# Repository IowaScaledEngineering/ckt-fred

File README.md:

# ckt-fred
Circuit for Battery/Track Powered FRED

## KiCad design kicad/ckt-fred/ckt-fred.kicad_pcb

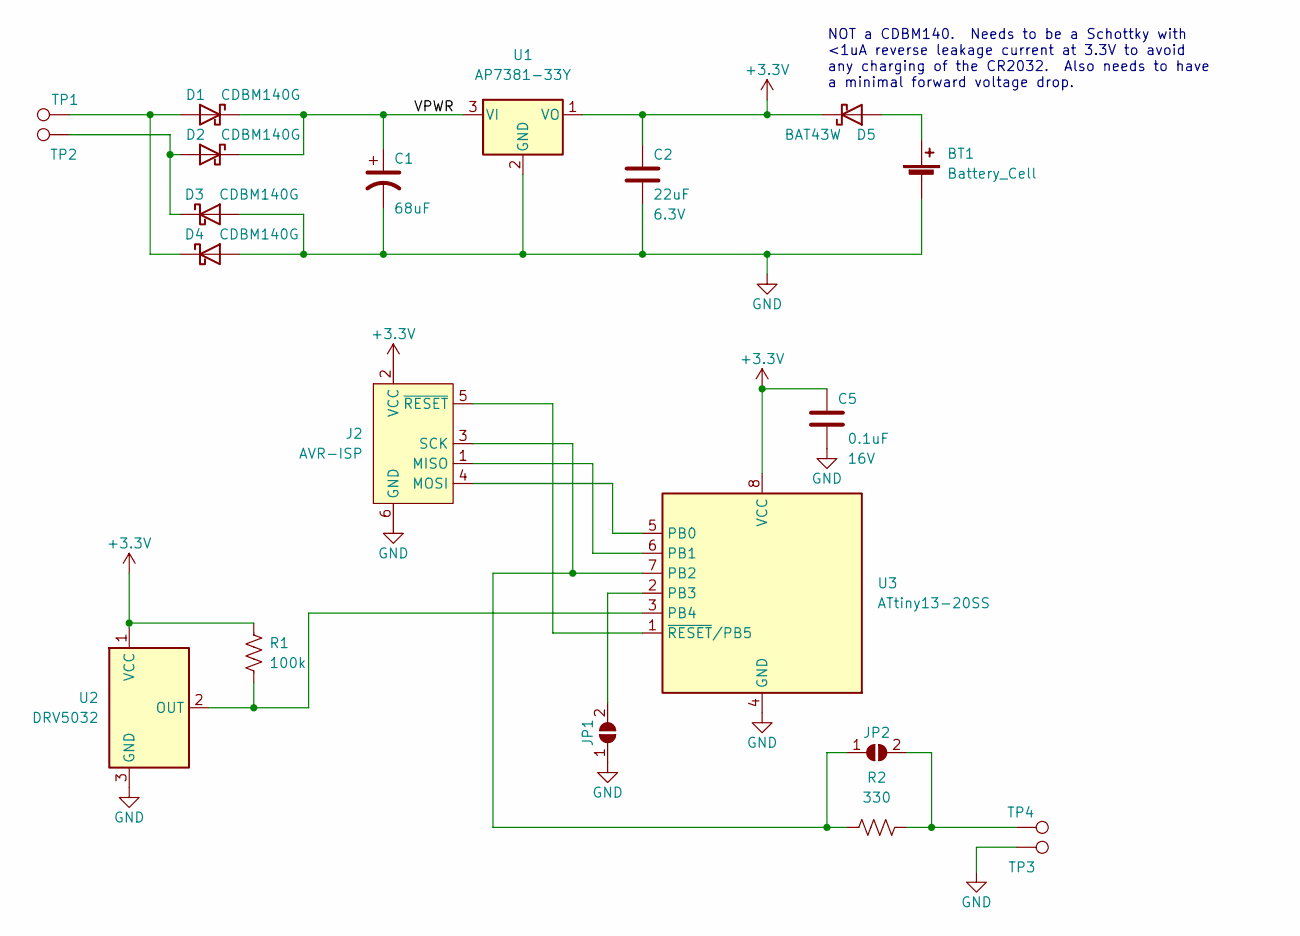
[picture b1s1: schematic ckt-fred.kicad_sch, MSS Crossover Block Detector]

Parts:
BT1: Battery_Cell; BatteryHolder_Keystone_3034_1x20mm
C1: 68uF; CP_Elec_6.3x5.8
C2: 22uF; C_0805_2012Metric; Voltage 6.3V
C5: 0.1uF; C_0805_2012Metric; Voltage 16V
D1, D2, D3, D4: CDBM140G; SOD-123T
D5: BAT43W; SOD-123T
J2: AVR-ISP; Tag-Connect_TC2030-IDC-NL_2x03_P1.27mm_Vertical
JP1, JP2: SolderJumper_2_Open; SolderJumper-2_P1.3mm_Open_RoundedPad1.0x1.5mm
R1: 100k; R_0805_2012Metric
R2: 330; R_0805_2012Metric
TP1, TP2, TP3, TP4: TestPoint; TestPoint_Pad_4.0x4.0mm
U1: AP7381-33Y; SOT-89-3
U2: DRV5032; SOT-23
U3: ATtiny13-20SS; SOIC-8_3.9x4.9mm_P1.27mm

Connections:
+3.3V: C2.1, C5.1, D5.1 (K), J2.2 (VCC), R1.1, U1.1 (VO), U2.1 (VCC), U3.8 (VCC)
/VPWR: C1.1, D1.1 (K), D2.1 (K), U1.3 (VI)
GND: BT1.2 (-), C1.2, C2.2, C5.2, D3.2 (A), D4.2 (A), J2.6 (GND), JP1.1 (A), TP3.1, U1.2 (GND), U2.3 (GND), U3.4 (GND)
unnamed: BT1.1 (+), D5.2 (A)
unnamed: D1.2 (A), D4.1 (K), TP1.1
unnamed: D2.2 (A), D3.1 (K), TP2.1
unnamed: J2.1 (MISO), U3.6 (PB1)
unnamed: J2.3 (SCK), JP2.1 (A), R2.1, U3.7 (PB2)
unnamed: J2.4 (MOSI), U3.5 (PB0)
unnamed: J2.5 (~RESET), U3.1 (~RESET/PB5)
unnamed: JP1.2 (B), U3.2 (PB3)
unnamed: R1.2, U2.2 (OUT), U3.3 (PB4)
unnamed: JP2.2 (B), R2.2, TP4.1

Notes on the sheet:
NOT a CDBM140. Needs to be a Schottky with <1uA reverse leakage current at 3.3V to avoid any charging of the CR2032. Also needs to have a minimal forward voltage drop.

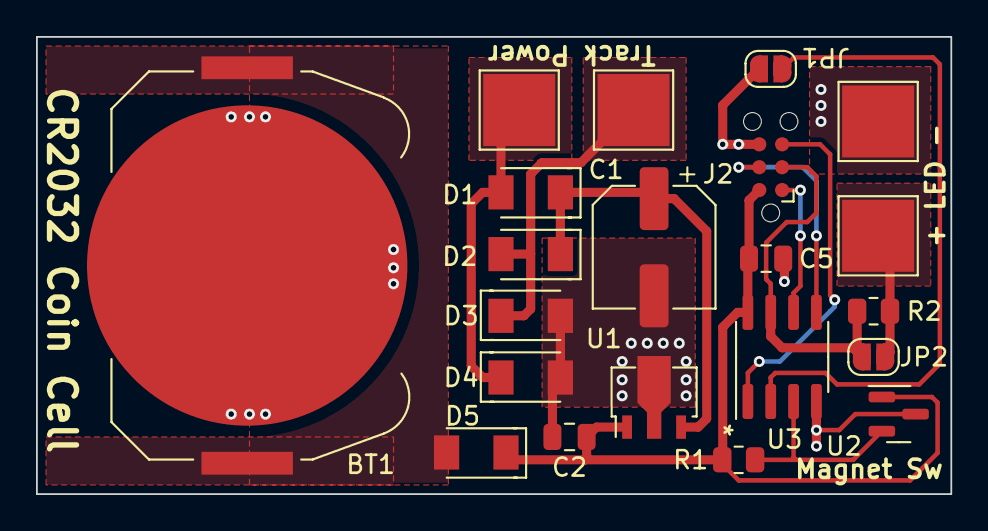
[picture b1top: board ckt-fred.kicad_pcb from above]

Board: 2 copper layers, 50.8 x 25.4 mm, 21 parts (0 on the bottom side), 13 nets.

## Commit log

2024-08-14 Just an initial draft of something to shoot at
2024-09-11 Start of FRED PCB
2024-09-11 A few updates
2024-09-26 Add output jumper to bypass resistor

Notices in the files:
kicad/ckt-fred/ckt-fred.kicad_pcb:
CC BY-SA ©2024
